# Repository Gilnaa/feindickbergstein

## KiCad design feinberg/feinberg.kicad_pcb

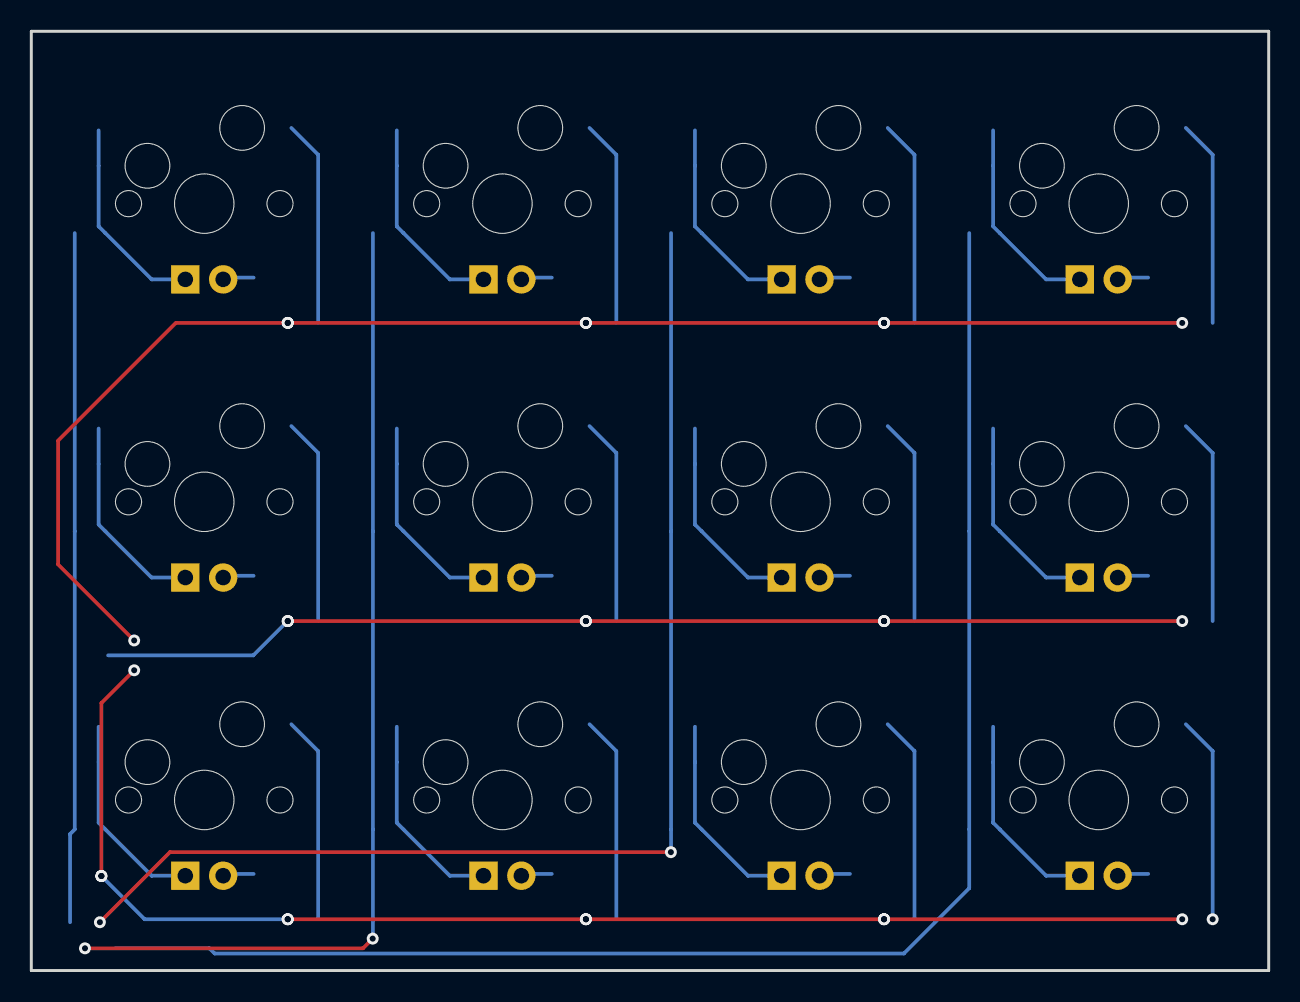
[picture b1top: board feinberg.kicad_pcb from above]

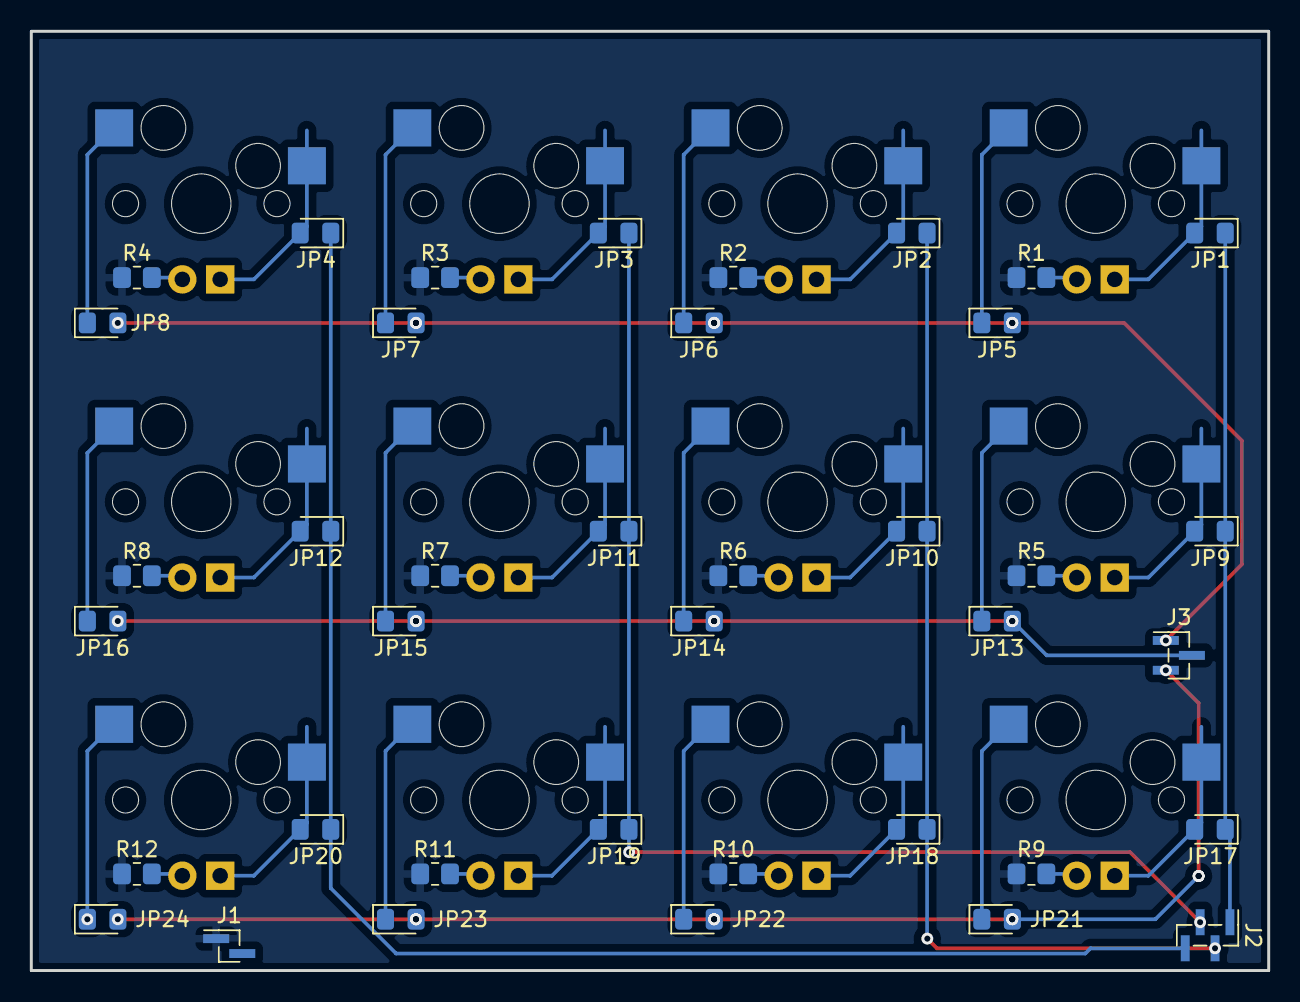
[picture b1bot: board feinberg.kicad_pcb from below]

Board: 2 copper layers, 83.0 x 63.0 mm, 51 parts (39 on the bottom side), 44 nets.

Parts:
J1: Conn_01x02_Male; PinHeader_1x02_P1.00mm_Vertical_SMD_Pin1Left
J2: Conn_01x04_Male; PinHeader_1x04_P1.00mm_Vertical_SMD_Pin1Left
J3: Conn_01x03_Male; PinHeader_1x03_P1.00mm_Vertical_SMD_Pin1Left
JP1, JP2, JP3, JP4, JP5, JP6, JP7, JP8, JP9, JP10, JP11, JP12, JP13, JP14, JP15, JP16, JP17, JP18, JP19, JP20, JP21, JP22, JP23, JP24: SolderJumper_2_Open; D_0805_2012Metric_Pad1.15x1.40mm_HandSolder
R1, R2, R3, R4, R5, R6, R7, R8, R9, R10, R11, R12: R; R_0805_2012Metric_Pad1.20x1.40mm_HandSolder
SW1, SW2, SW3, SW4, SW5, SW6, SW7, SW8, SW9, SW10, SW11, SW12: SW_Push; MXOnly-1U-FLIPPED-Hotswap-LED

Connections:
5V: J1.1, R1.1, R2.1, R3.1, R4.1, R5.1, R6.1, R7.1, R8.1, R9.1, R10.1, R11.1, R12.1
COL0: J2.1, JP1.1 (A), JP9.1 (A), JP17.1 (A)
COL1: J2.2, JP2.1 (A), JP10.1 (A), JP18.1 (A)
COL2: J2.3, JP3.1 (A), JP11.1 (A), JP19.1 (A)
COL3: J2.4, JP4.1 (A), JP12.1 (A), JP20.1 (A)
unnamed: JP1.2 (B), SW1.1 (COL), SW1.4 (LEDGND)
unnamed: JP2.2 (B), SW2.1 (COL), SW2.4 (LEDGND)
unnamed: JP3.2 (B), SW3.1 (COL), SW3.4 (LEDGND)
unnamed: JP4.2 (B), SW4.1 (COL), SW4.4 (LEDGND)
unnamed: JP5.1 (A), SW1.2 (ROW)
unnamed: JP6.1 (A), SW2.2 (ROW)
unnamed: JP7.1 (A), SW3.2 (ROW)
unnamed: JP8.1 (A), SW4.2 (ROW)
unnamed: JP9.2 (B), SW5.1 (COL), SW5.4 (LEDGND)
unnamed: JP10.2 (B), SW6.1 (COL), SW6.4 (LEDGND)
unnamed: JP11.2 (B), SW7.1 (COL), SW7.4 (LEDGND)
unnamed: JP12.2 (B), SW8.1 (COL), SW8.4 (LEDGND)
unnamed: JP13.1 (A), SW5.2 (ROW)
unnamed: JP14.1 (A), SW6.2 (ROW)
unnamed: JP15.1 (A), SW7.2 (ROW)
unnamed: JP16.1 (A), SW8.2 (ROW)
unnamed: JP17.2 (B), SW9.1 (COL), SW9.4 (LEDGND)
unnamed: JP18.2 (B), SW10.1 (COL), SW10.4 (LEDGND)
unnamed: JP19.2 (B), SW11.1 (COL), SW11.4 (LEDGND)
unnamed: JP20.2 (B), SW12.1 (COL), SW12.4 (LEDGND)
unnamed: JP21.1 (A), SW9.2 (ROW)
unnamed: JP22.1 (A), SW10.2 (ROW)
unnamed: JP23.1 (A), SW11.2 (ROW)
unnamed: JP24.1 (A), SW12.2 (ROW)
unnamed: R1.2, SW1.3 (LED)
unnamed: R2.2, SW2.3 (LED)
unnamed: R3.2, SW3.3 (LED)
unnamed: R4.2, SW4.3 (LED)
unnamed: R5.2, SW5.3 (LED)
unnamed: R6.2, SW6.3 (LED)
unnamed: R7.2, SW7.3 (LED)
unnamed: R8.2, SW8.3 (LED)
unnamed: R9.2, SW9.3 (LED)
unnamed: R10.2, SW10.3 (LED)
unnamed: R11.2, SW11.3 (LED)
unnamed: R12.2, SW12.3 (LED)
ROW0: J3.1, JP5.2 (B), JP6.2 (B), JP7.2 (B), JP8.2 (B)
ROW1: J3.2, JP13.2 (B), JP14.2 (B), JP15.2 (B), JP16.2 (B)
ROW2: J3.3, JP21.2 (B), JP22.2 (B), JP23.2 (B), JP24.2 (B)

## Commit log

2022-10-03 Initial thingie
2022-10-03 dicksteining
